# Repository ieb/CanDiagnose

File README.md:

# Can Diagnose

Runs on a ESP32 with a webserver exposing an API to diagnose and monitor CanBus traffic.
Based on Datadisplay and DeviceAnalyser from the NMEA2000 libraries.

* [x] Setup Wifi
* [x] Setup MDNS registration
* [x] Implement webserver
* [x] Serve files from Flash (SPIFFS)
* [x] Implement data api /api/data/<n> where n == 0-10.
* [x] Expose set of standard CAN messages on /api/data
* [x] Implement simple UI in Javascript hosted on SPIFFS, targetting eink and normal browsers (based on SignalK eink)
* [x] Implement BPM280 source
* [x] Implement calibration mechanism using DAC
* [Fail] Implement ADC Source

The ESP32 ADC source cannot be made reliable enough or accurate enough to be used to monitor a battery. 
It is possible to get down to a 0.2% error with a callibrated lookup table, however the ADC mechamism (Sucessive Aproximation Register)
produced noisy values that are frequetly as much as +- 3%. At 12.6v this is 0.4v which is unworkable. Offsetting the voltage with a precision opamp so the ESP32 reads from 11 to 15v would reduce this to 0.15v, however this is still to large to be usable. Multi sampling helps generate a stable reading, however this requires 64 samples with a /5 moving average so over at least 60s. This does give and acceptable accuracy, but the speed of measuring the voltage is close to unworkable.

All attenuations were tried, and 1,2,4,16,32,64 clock divisions were tried to see if the rate of the SAR made any difference. It does not appear to change the results.

On that basis, I am giving up on using the ESP32 ADC for this purpose.

It still provides a good platform for a Wifi data server, and Can reader.

* [x] Redesign PCB to use 16bit ADC over i2c  (ADS1115)
* [x] Implement ADC sensor code.  
* [x] Implement admin interface.
* [x] Support configuration and calibration via web browser.
* [x] Support Configuraiton of single and differential ADC.
* [x] Add OLED display 
* [x] Add touch sensor to control oled display
* [x] Bench Calibrate expecialy shunt
* [x] Install test and calibrate. - Failed, the distance beween the board and the batteries is too great to get reliable shunt measurements.
* [x] Investigate using a shunt amplifier as used by VRA Alternator controll
* [x] Implement remote battery sensor using Modbus  (see BatterySensor project)
* [x] Reimplement PCB to have no BME280 and no ADS1115 replacing with a RS485 interface to ModBus devices.  (see CanPressure for Can based pressure, humidity, temperature sensor)
* [x] Implement Modbus master

# Usage

The device will boot and connect to wifi controlled by its burned in config file (data/config.txt). 
There are 2 modes it can run in, a WiFi client or a AP. If its configured to be an AP, then join its network. If its a client find its ip. From now on this will be <ip>

Go to its ip on http://<ip> and you will see a data view of the data it is capturing.
Go to http://<ip>/admin.html and you will see a admin view with the ability to upload a new configuration file and reboot.

Both these views ae SPAs served from static files burned into the ESP32 Flash using APIs.

Connecting to the serial port monitor allows lower level control and diagnostics, enter 'h<CR>' to get help.

# Developing

Project uses PlatformIO in VSCode.  WebUI is in  ui/einkweb with build files added to data/ to be built into a flash image using ./buidui.sh

## PIO commands

because I alwaysforget.

* pio run -t upload
* pio device monitor

See buildui.sh for SPIFFS image commands.

# Connectors

    ---------------------------------------------
    |           a b c d e f g h                 |
    |  A                                        |
    |  B                                        |
    |  C                                        |
    |  D                                     H  |
    |  E                                     I  |
    |  F                                     J  |
    |  G           i j k l m                 K  |
    ---------------------------------------------

    a  SPI BL   GPIO13
    b  SPI RST  GPIO12
    c  SPI DC   GPIO26
    d  SPI CS   GPIO25
    e  SPI SCK  GPIO33
    f  SPI MOSI GPIO32
    g  SPI GND  
    h  SPI 3V    
    i  i2c GND      Display black/blue
    j  i2c SCL  D5    Display green
    k  i2c SDA  D18    Display white
    l  i2c BTN  D19    Display yellow
    m  i2c 3V       Display red

    A  1wire 1w  D21
    B  1wire GND
    C  1wire 3V
    D  RS-485 5.8V
    E  RS-485 GND
    F  RS-485 A 
    G  RS-485 B
    H  CAN 12V
    I  CAN 0V
    J  CAN CANH
    K  CAN CANL

    Other Pins Not mentioned above
    RS485-TX TX2/GPIO17
    RS485-RX RX2/GPIO16
    RS485-EN D4
    CAN-RX  D22
    CAN-TX  D23

# eInk Waveshare display

This uses SPI output only with a bunch of additional pins.

    eInk DIN <-  f  SPI MOSI GPIO32
    eInk CLK <-  e  SPI SCK  GPIO33
    eInk CS  <-  d  SPI CS   GPIO25
    eInk DC  <-  c  SPI DC   GPIO26
    eInk RST <-  b  SPI RST  GPIO12
    eInk BUSY -> a  SPI BL   GPIO13

# 4 inch TFT display 480x320 24 bit colour driven by a ILI9488 driver.

uses SPI + a PWM blacklight. Control via a TPP233 Touch switch. Library is TFT_eSPI library. Pin mappings defined as compile definitions.

    -D TFT_MISO=GPIO_NUM_35
    -D TFT_MOSI=GPIO_NUM_32
    -D TFT_SCLK=GPIO_NUM_33
    -D TFT_CS=GPIO_NUM_25
    -D TFT_DC=GPIO_NUM_26
    -D TFT_RST=GPIO_NUM_27
    -D TFT_PWM_BL=GPIO_NUM_14
    -D ILI9488_DRIVER

The display sleeps after 60s of inactivity to reduce power drain, but turning off the backlight. Sleeping the IMI9488 driver has not been done as of yet.  Pages are implemented as classes using widgets. When a page is selected it is allocated into heap and does not exist while not displaying. On other drivers here all pages were compiled in, however the RAM usage is higher on account of full colour and display size. 

In most cases attempts to update the screen, on screen causes flickering so double buffering of updates is done using sprits with DMA transfers from the sprite to the screen. Images for screen are stored in jpg on flash, consuming about 30KB per screen.

Drawing to sprites also works in 1bpp, 4bpp or 16bpp.

## TFT case

3d printed case, with 2 touch sensors and round shielded cable, as ribbon will emit too much interference to nearby devices. 

Wires

|| color || designation || ESP32 Pin ||
---------------------------------------
| Red    |  5v          | 5v           |
| black  |  0v          | 0v           |
| pink   |  CS          | GPIO_NUM_25  |
| cyan   |  Reset       | GPIO_NUM_27  |
| white  |  DC/RS       | GPIO_NUM_26  |
| blue   |  SDI(MOSI)   | GPIO_NUM_32  |
| green  |  SCK         | GPIO_NUM_33  |
| grey   |  LED         | GPIO_NUM_14  |
| Purple |  SDO(MISO)   | GPIO_NUM_35  |
| Orange |  3.3v        | 3.3v         |
| Brown  | Touch Lower  | GPIO_NUM_19  |
| Yellow | Touch Top    | TBD          |

Due to the additional touch pins a fresh PCB is probably needed.

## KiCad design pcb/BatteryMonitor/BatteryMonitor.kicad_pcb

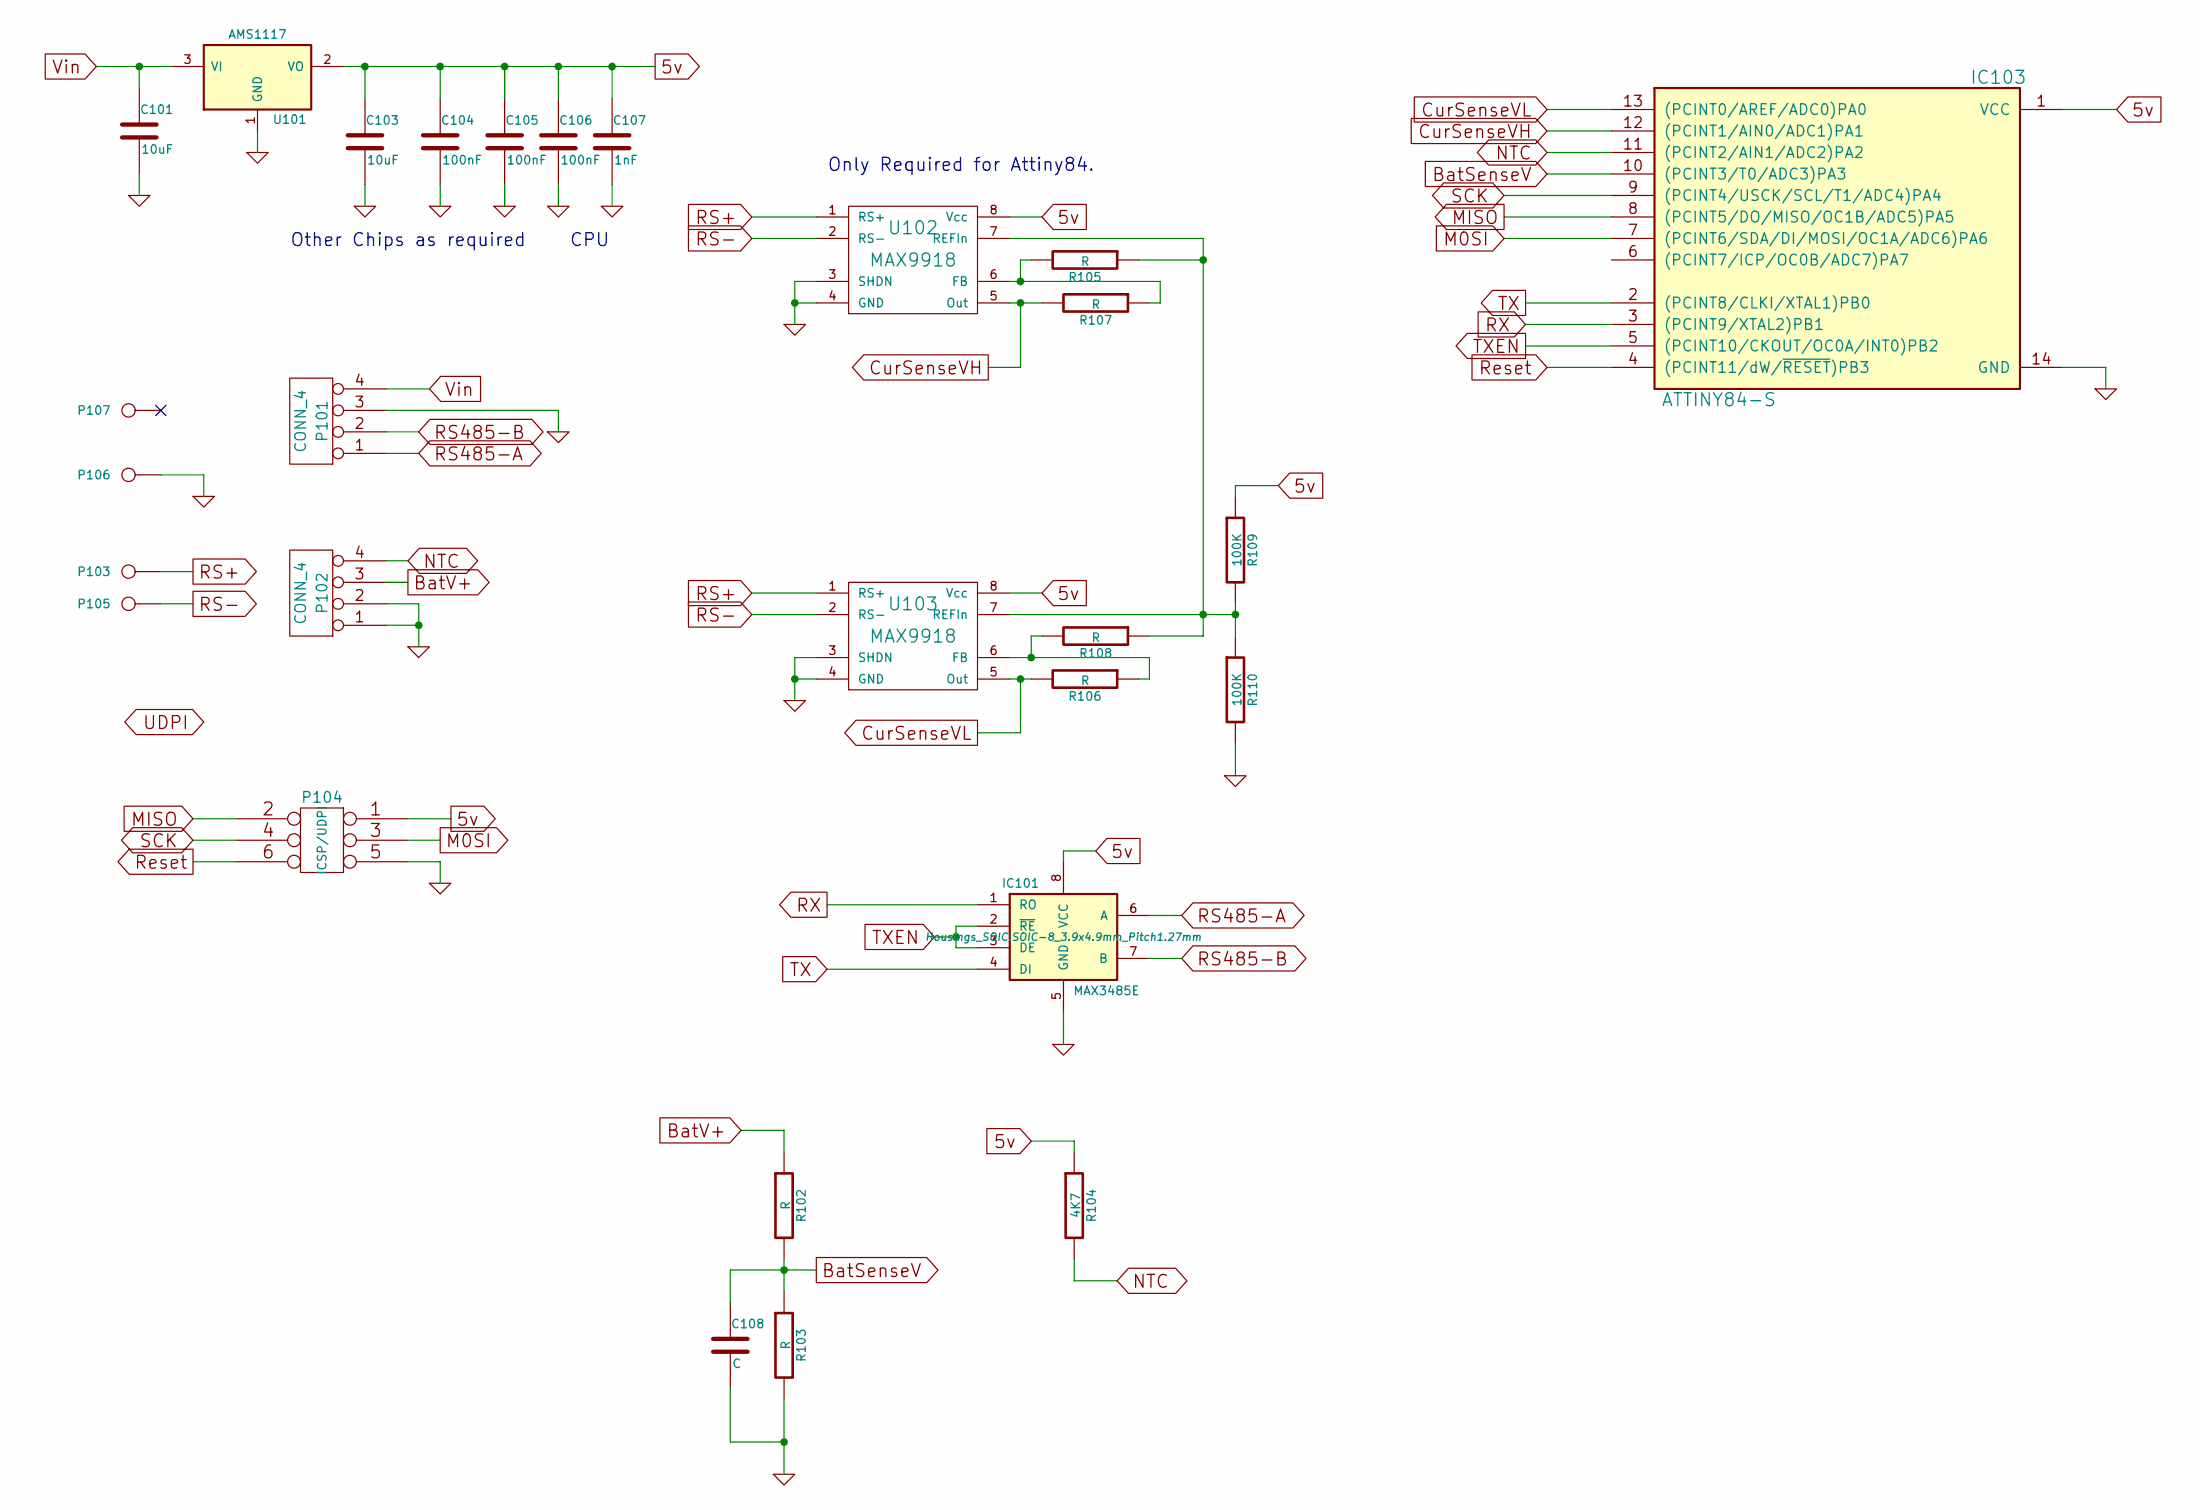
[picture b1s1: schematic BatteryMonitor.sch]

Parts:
C101, C103: 10uF; C_1206
C104, C105, C106: 100nF; C_0805
C107: 1nF; C_0805
C108: C; C_0805
IC101: MAX3485E; SOIC-8_3.9x4.9mm_Pitch1.27mm
IC103: ATTINY84-S; DIP-14_W7.62mm
P101, P102: CONN_4; bornier4
P103, P106, P107: RS+; 1pin
P104: ICSP/UDPI; Pin_Header_Straight_2x03
P105: RS-; 1pin
R102, R103, R105, R106, R107, R108: R; R_0805
R104: 4K7; R_0805
R109, R110: 100K; R_0805
U101: AMS1117; SOT-223-3Lead_TabPin2
U102, U103: MAX9918; SOIC-8_3.9x4.9mm_Pitch1.27mm

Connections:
5v: C103.1, C104.1, C105.1, C106.1, C107.1, IC101.8 (VCC), IC103.1 (VCC), P104.1, R104.1, R109.1, U101.2 (VO), U102.8 (Vcc), U103.8 (Vcc)
BatSenseV: C108.1, IC103.10 ((PCINT3/T0/ADC3)PA3), R102.2, R103.1
BatV+: P102.3, R102.1
CurSenseVH: IC103.12 ((PCINT1/AIN0/ADC1)PA1), R107.2, U102.5 (Out)
CurSenseVL: IC103.13 ((PCINT0/AREF/ADC0)PA0), R106.2, U103.5 (Out)
GND: C101.2, C103.2, C104.2, C105.2, C106.2, C107.2, C108.2, IC101.5 (GND), IC103.14 (GND), P101.3, P102.1, P102.2, P104.5, P106.1, R103.2, R110.2, U101.1 (GND), U102.3 (SHDN), U102.4 (GND), U103.3 (SHDN), U103.4 (GND)
M0SI: IC103.7 ((PCINT6/SDA/DI/MOSI/OC1A/ADC6)PA6), P104.3
MISO: IC103.8 ((PCINT5/DO/MISO/OC1B/ADC5)PA5), P104.2
NTC: IC103.11 ((PCINT2/AIN1/ADC2)PA2), P102.4, R104.2
unnamed: R105.1, R108.1, R109.2, R110.1, U102.7 (REFIn), U103.7 (REFIn)
unnamed: R105.2, R107.1, U102.6 (FB)
unnamed: R106.1, R108.2, U103.6 (FB)
RS485-A: IC101.6 (A), P101.1
RS485-B: IC101.7 (B), P101.2
RS+: P103.1, U102.1 (RS+), U103.1 (RS+)
RS-: P105.1, U102.2 (RS-), U103.2 (RS-)
RX: IC101.1 (RO), IC103.3 ((PCINT9/XTAL2)PB1)
Reset: IC103.4 ((PCINT11/dW/~RESET~)PB3), P104.6
SCK: IC103.9 ((PCINT4/USCK/SCL/T1/ADC4)PA4), P104.4
TX: IC101.4 (DI), IC103.2 ((PCINT8/CLKI/XTAL1)PB0)
TXEN: IC101.2 (~RE~), IC101.3 (DE), IC103.5 ((PCINT10/CKOUT/OC0A/INT0)PB2)
Vin: C101.1, P101.4, U101.3 (VI)

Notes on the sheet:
Only Required for Attiny84.
CPU
Other Chips as required

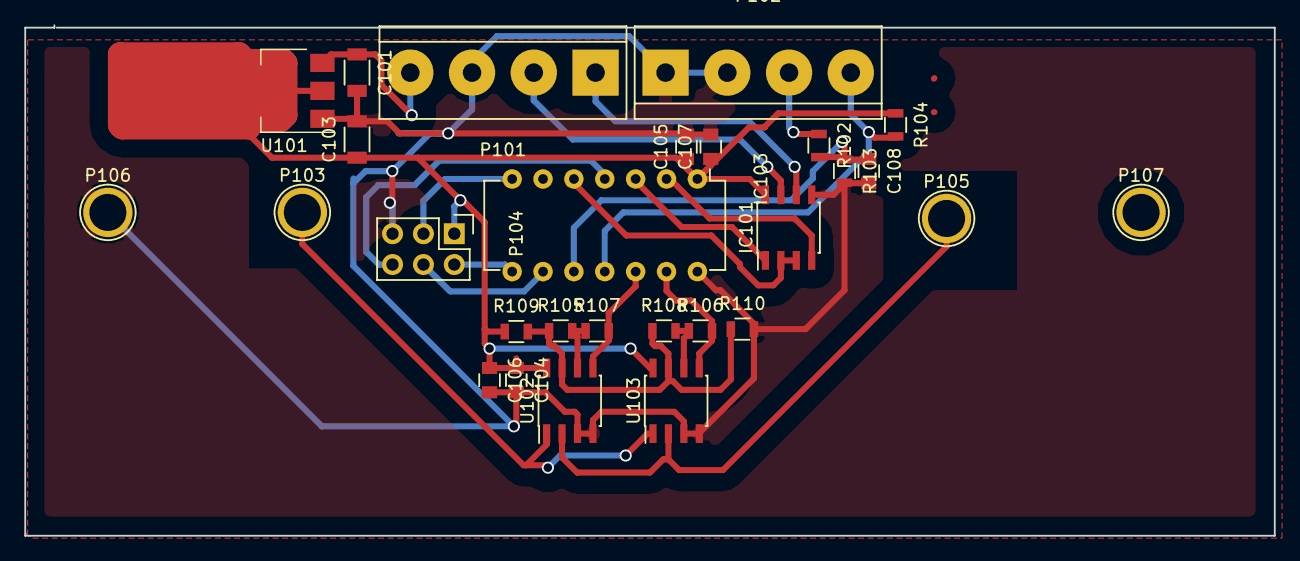
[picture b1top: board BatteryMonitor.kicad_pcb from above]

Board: 2 copper layers, 102.8 x 42.0 mm, 28 parts (0 on the bottom side), 22 nets.

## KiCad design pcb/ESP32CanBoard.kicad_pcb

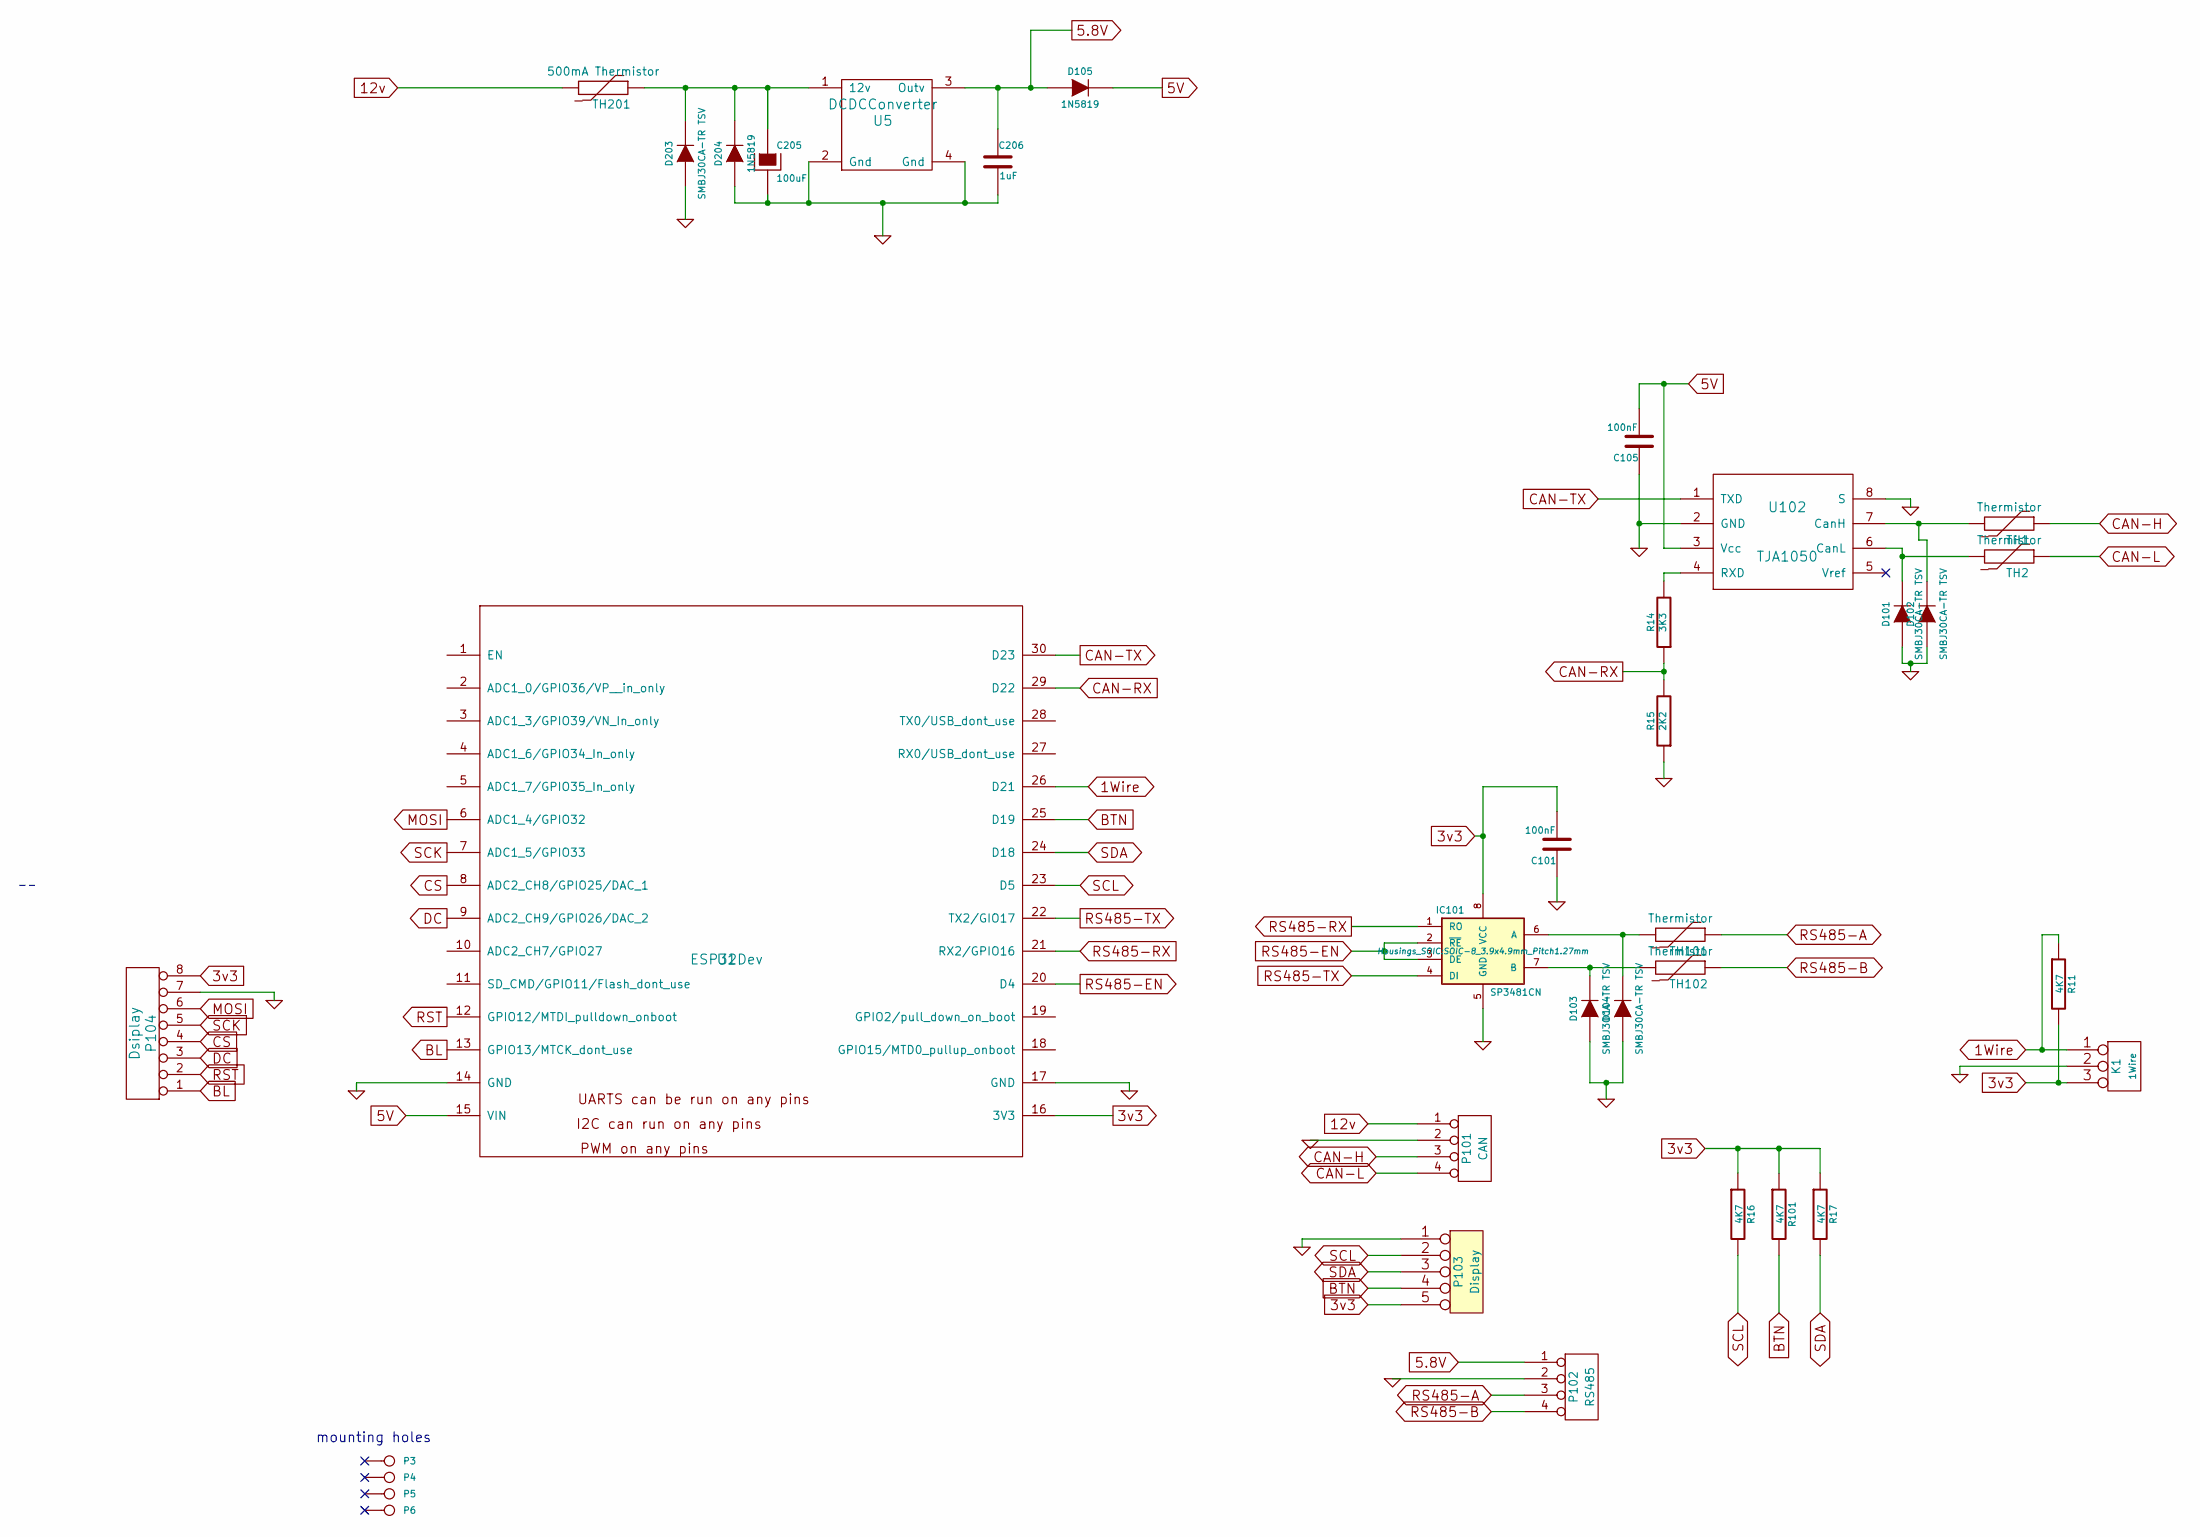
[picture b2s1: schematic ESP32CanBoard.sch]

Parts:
C101, C105: 100nF; C_0805
C205: 100uF; C_1210
C206: 1uF; C_1210
D101, D102, D103, D104, D203: SMBJ30CA-TR TSV; DO-214AB
D105, D204: 1N5819; D_1206
IC101: SP3481CN; SOIC-8_3.9x4.9mm_Pitch1.27mm
K1: 1Wire; bornier3
P3, P4, P5, P6: CONN_1; 1pin
P101: CAN; bornier4
P102: RS485; bornier4
P103: Display; Pin_Header_Straight_1x05
P104: Dsiplay; Pin_Header_Straight_1x08
R11, R16, R17, R101: 4K7; R_0805
R14: 3K3; R_0805
R15: 2K2; R_0805
TH1, TH2, TH101, TH102: Thermistor; R_1812
TH201: 500mA Thermistor; Resistor_Horizontal_RM7mm
U1: ESP32Dev
U5: DCDCConverter; DC-DC-Converter
U102: TJA1050; SOIC-8_3.9x4.9mm_Pitch1.27mm

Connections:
1Wire: K1.1, R11.1, U1.26 (D21)
3v3: C101.2, IC101.8 (VCC), K1.3, P103.5, P104.8, R11.2, R16.1, R17.1, R101.1, U1.16 (3V3)
5.8V: C206.1, D105.1 (A), P102.1, U5.3 (Outv)
5V: C105.2, D105.2 (K), U1.15 (VIN), U102.3 (Vcc)
12v: P101.1, TH201.2
BL: P104.1, U1.13 (GPIO13/MTCK_dont_use)
BTN: P103.4, R101.2, U1.25 (D19)
CAN-H: P101.3, TH1.1
CAN-L: P101.4, TH2.1
CAN-RX: R14.1, R15.2, U1.29 (D22)
CAN-TX: U1.30 (D23), U102.1 (TXD)
CS: P104.4, U1.8 (ADC2_CH8/GPIO25/DAC_1)
DC: P104.3, U1.9 (ADC2_CH9/GPIO26/DAC_2)
GND: C101.1, C105.1, C205.2, C206.2, D101.1 (A), D102.1 (A), D103.1 (A), D104.1 (A), D203.1 (A), D204.1 (A), IC101.5 (GND), K1.2 (PM), P101.2, P102.2, P103.1, P104.7, R15.1, U1.14 (GND), U1.17 (GND), U5.2 (Gnd), U5.4 (Gnd), U102.2 (GND), U102.8 (S)
MOSI: P104.6, U1.6 (ADC1_4/GPIO32)
unnamed: C205.1, D203.2 (K), D204.2 (K), TH201.1, U5.1 (12v)
unnamed: D101.2 (K), TH2.2, U102.6 (CanL)
unnamed: D102.2 (K), TH1.2, U102.7 (CanH)
unnamed: D103.2 (K), IC101.7 (B), TH102.2
unnamed: D104.2 (K), IC101.6 (A), TH101.2
unnamed: R14.2, U102.4 (RXD)
RS485-A: P102.3, TH101.1
RS485-B: P102.4, TH102.1
RS485-EN: IC101.2 (~RE~), IC101.3 (DE), U1.20 (D4)
RS485-RX: IC101.1 (RO), U1.21 (RX2/GPIO16)
RS485-TX: IC101.4 (DI), U1.22 (TX2/GIO17)
RST: P104.2, U1.12 (GPIO12/MTDI_pulldown_onboot)
SCK: P104.5, U1.7 (ADC1_5/GPIO33)
SCL: P103.2, R16.2, U1.23 (D5)
SDA: P103.3, R17.2, U1.24 (D18)

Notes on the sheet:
mounting holes

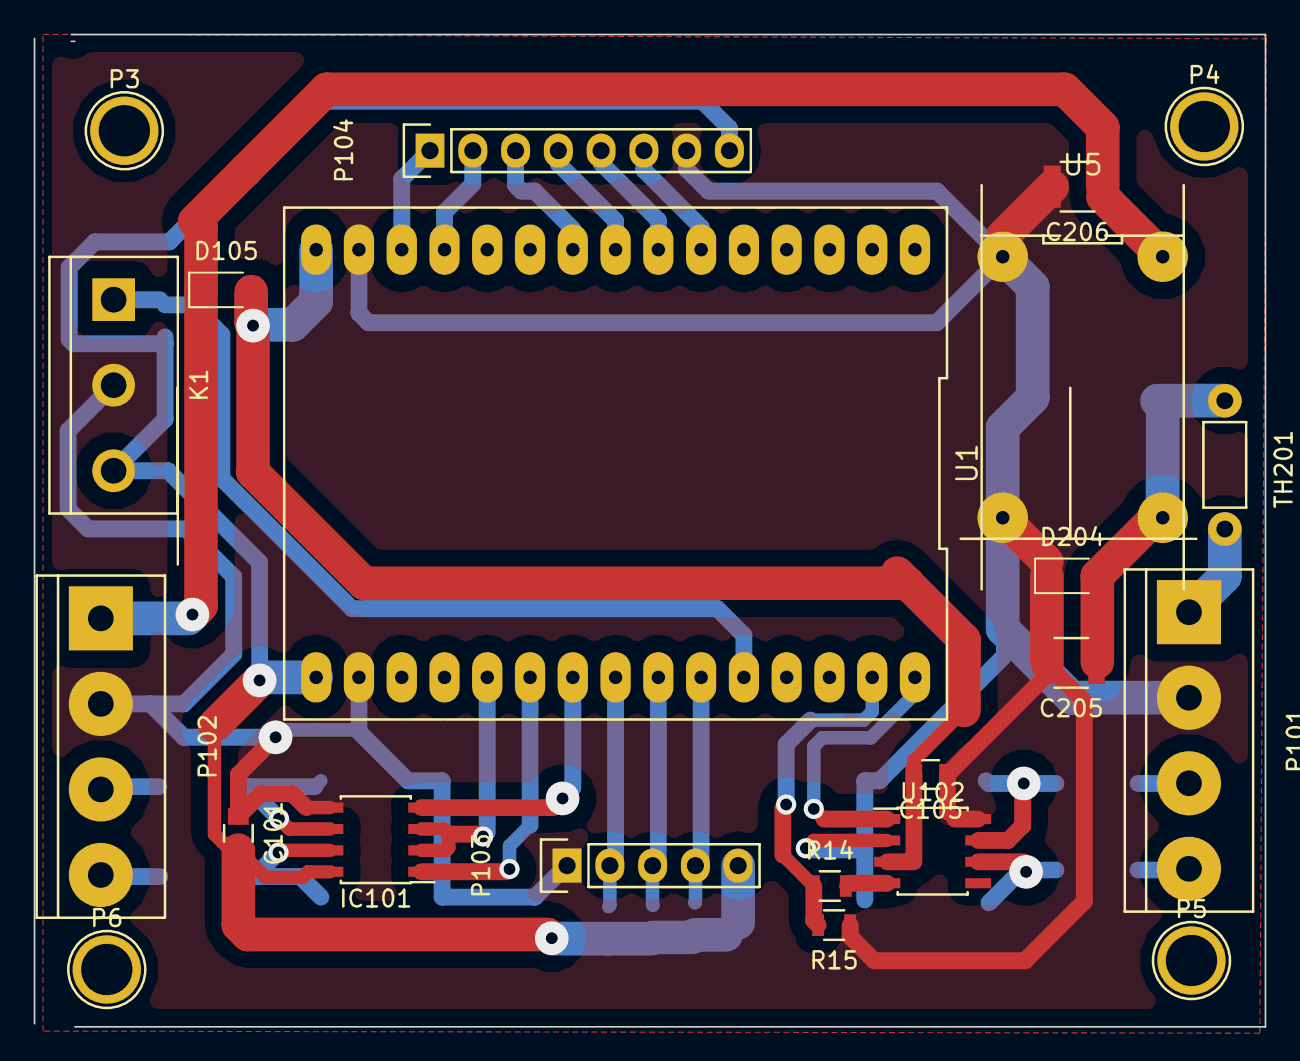
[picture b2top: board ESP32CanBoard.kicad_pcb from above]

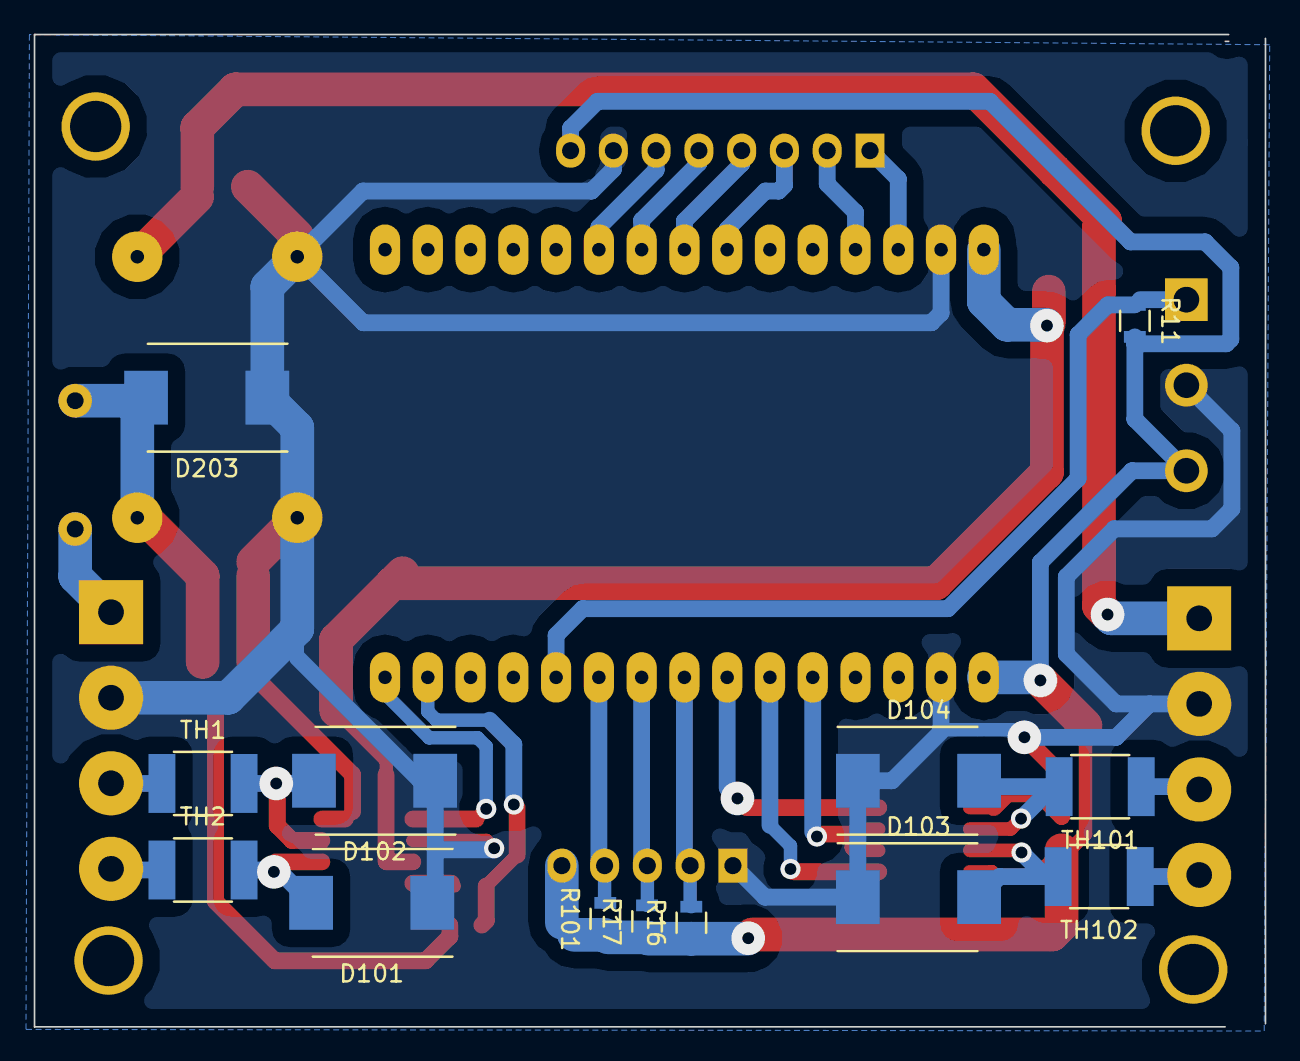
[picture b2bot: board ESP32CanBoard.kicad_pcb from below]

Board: 2 copper layers, 73.1 x 58.9 mm, 35 parts (13 on the bottom side), 30 nets.

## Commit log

2021-10-27 Inital commit, well not really, clean repo
2021-10-30 Added dataoutput over bluetooth
2021-11-06 Added ESP32Can pcb
2021-11-12 Just before switching away from ESP32 ADC
2021-11-15 Started work on ui for eink devices
2021-11-17 Working version served from flash disk
2021-11-18 Added basic admin interface over http, todo auth
2021-11-20 Added configuration from file, and admin authorization
2021-11-21 Added admin interface, fixed esp32 panic
2021-11-21 Updated readmes
2021-11-22 Now starts as a SoftAP with when WiFi fails to allow config
2021-11-27 Added Oled display with logo and cycling output
2021-12-06 Estended display capabilities
2021-12-15 Added 24h history for pressure and logbook recording to flash
2021-12-29 Added Logging, fixed dome bugs with a read feed of packets
2022-05-06 Added CSV Output for Kindle booklet
2022-05-12 Fixed CSV output
2022-07-13 New board, moved bme280 to CanPressure board
2022-07-15 New board operational using Modbus BatterySensors and CanPressure board
2022-07-15 Fixed display
2022-07-16 NMEA2000 ESP does not set pins correctly as documented where there are libraries building
2022-07-18 Added display pages and fixed ui
2022-07-18 Fixe baromter display and logbook
2022-07-18 Fixed logfile and lat long precision
2022-07-20 added time display and stopped listing devices on start
2022-11-17 Added 3.7 Waveshare eink display
2023-01-01 Adapted to new modbus shunt modules and tested over 10m wire
2023-01-24 Cleaned up display structure in prep for TFT
2023-02-02 Added TFT display module, and made Modbusmaster non blocking
2023-02-07 save after ide crash
2023-02-11 Using sprites and double buffering to elimiante flicker on update
2023-02-11 Added splash screen logo
2023-02-11 Implemented sleep mode for the tft display
2023-02-12 Fixed wakeup behaviour
2023-02-15 added animated dial using jpg background
2023-02-21 Added coolant and fuel guages
2023-02-24 Fixed needle rendering and added lcd display
2023-03-02 Started to add sailing dial, compiles, not tested
2023-03-06 Added InfoText boxes to the sailing screen
2023-04-09 Added polar calculations for display
2023-09-09 Fixed 49day overflows
